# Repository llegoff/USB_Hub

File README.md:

[:fr:](LISEZMOI.md) [:uk:](README.md)

# USB_Hub
GL852G or GL850G usb2.0 hub PiZero format

GL852G is Multi TT hub chip

GL850G is Single TT hub chip

rev1
- R12 (new R3 in rev2) is connected to 5v, it must be connected to gnd

rev2
- Change R3 route
- Change the numbering of the components

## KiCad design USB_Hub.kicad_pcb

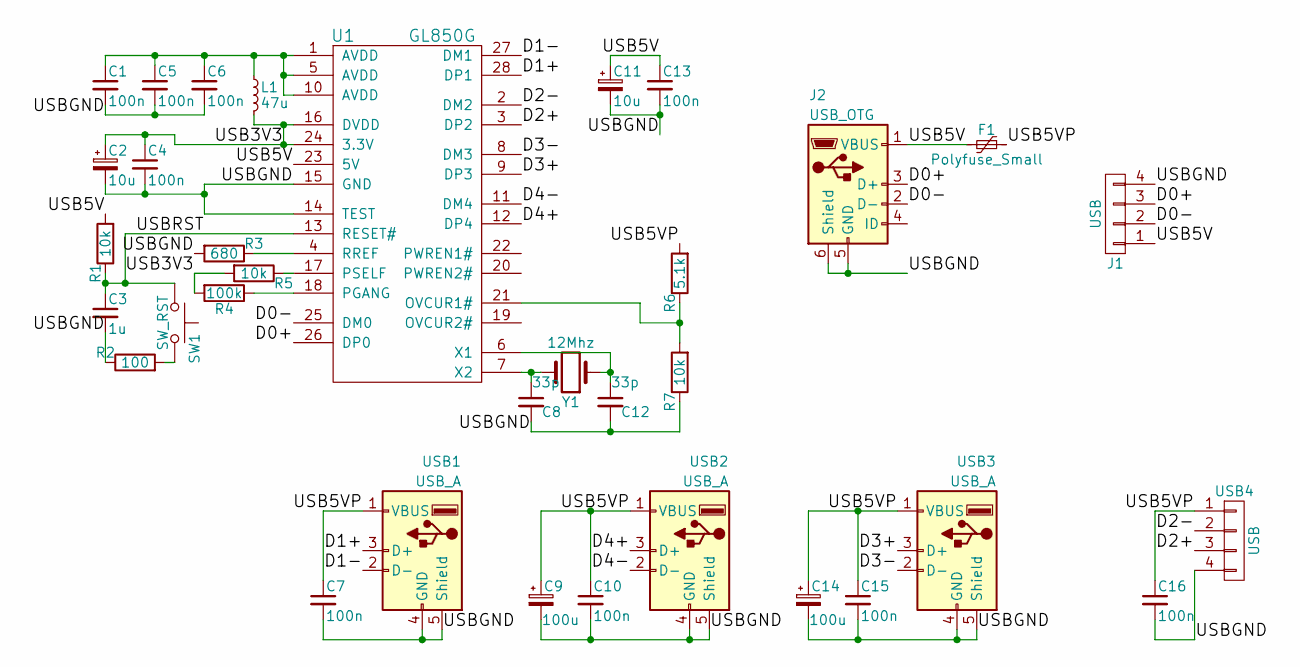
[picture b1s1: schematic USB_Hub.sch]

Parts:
C1, C4, C5, C6, C7, C10, C13, C15, C16: 100n; C_0805
C2, C11: 10u; CP_Elec_4x5.7
C3: 1u; C_0805
C8, C12: 33p; C_0805
C9, C14: 100u; CP_Elec_6.3x5.3
F1: Polyfuse_Small; Fuse_SMD1206_Reflow
J1: USB; Pin_Header_Straight_1x04_Pitch2.54mm
J2: USB_OTG; USB_Mini-B
L1: 47u; L_6.3x6.3_H3
R1, R5, R7: 10k; R_0805
R2: 100; R_0805
R3: 680; R_0805
R4: 100k; R_0805
R6: 5.1k; R_0805
SW1: SW_RST; SW_PUSH_6mm
U1: GL850G; SSOP-28_5.3x10.2mm_Pitch0.65mm
USB1, USB2, USB3: USB_A; USB_A_TTH&SMD
USB4: USB; Pin_Header_Straight_1x04_Pitch2.54mm
Y1: 12Mhz; Crystal_HC49-U_Vertical

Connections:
/D0+: J1.3, J2.3 (D+), U1.26 (DP0)
/D0-: J1.2, J2.2 (D-), U1.25 (DM0)
/D1+: U1.28 (DP1), USB1.3 (D+)
/D1-: U1.27 (DM1), USB1.2 (D-)
/D2+: U1.3 (DP2), USB4.3
/D2-: U1.2 (DM2), USB4.2
/D3+: U1.9 (DP3), USB3.3 (D+)
/D3-: U1.8 (DM3), USB3.2 (D-)
/D4+: U1.12 (DP4), USB2.3 (D+)
/D4-: U1.11 (DM4), USB2.2 (D-)
/USB3V3: C2.1, C4.1, L1.2, R4.2, R5.2, U1.16 (DVDD), U1.24 (3.3V)
/USB5V: C11.1, C13.1, F1.2, J1.1, J2.1 (VBUS), R1.2, U1.23 (5V)
/USB5VP: C7.1, C9.1, C10.1, C14.1, C15.1, C16.1, F1.1, R6.2, USB1.1 (VBUS), USB2.1 (VBUS), USB3.1 (VBUS), USB4.1
/USBGND: C1.2, C2.2, C3.2, C4.2, C5.2, C6.2, C7.2, C8.2, C9.2, C10.2, C11.2, C12.2, C13.2, C14.2, C15.2, C16.2, J1.4, J2.5 (GND), J2.6 (Shield), R2.1, R3.2, R7.1, U1.14 (TEST), U1.15 (GND), USB1.4 (GND), USB1.5 (Shield), USB2.4 (GND), USB2.5 (Shield), USB3.4 (GND), USB3.5 (Shield), USB4.4
/USBRST: C3.1, R1.1, SW1.1, U1.13 (RESET#)
unnamed: C1.1, C5.1, C6.1, L1.1, U1.1 (AVDD), U1.5 (AVDD), U1.10 (AVDD)
unnamed: C8.1, U1.7 (X2), Y1.2
unnamed: C12.1, U1.6 (X1), Y1.1
unnamed: R2.2, SW1.2
unnamed: R3.1, U1.4 (RREF)
unnamed: R4.1, U1.18 (PGANG)
unnamed: R5.1, U1.17 (PSELF)
unnamed: R6.1, R7.2, U1.21 (OVCUR1#)

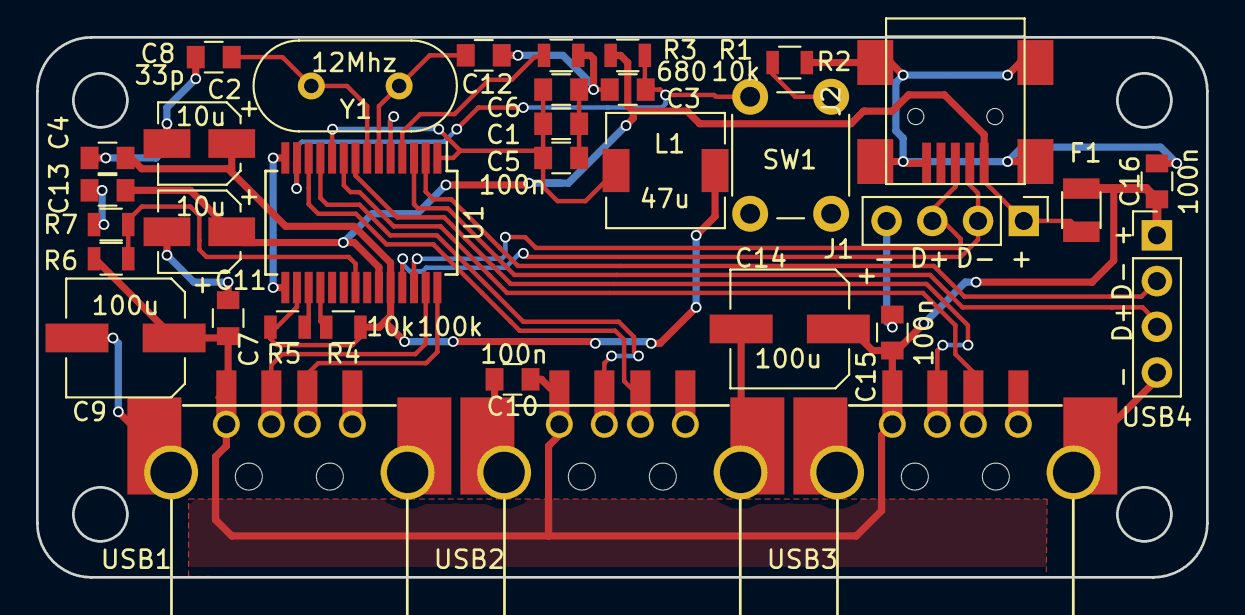
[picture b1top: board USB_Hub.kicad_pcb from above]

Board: 2 copper layers, 65.0 x 30.0 mm, 34 parts (0 on the bottom side), 23 nets.

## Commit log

2017-09-17 rev2
2018-09-17 gl852
